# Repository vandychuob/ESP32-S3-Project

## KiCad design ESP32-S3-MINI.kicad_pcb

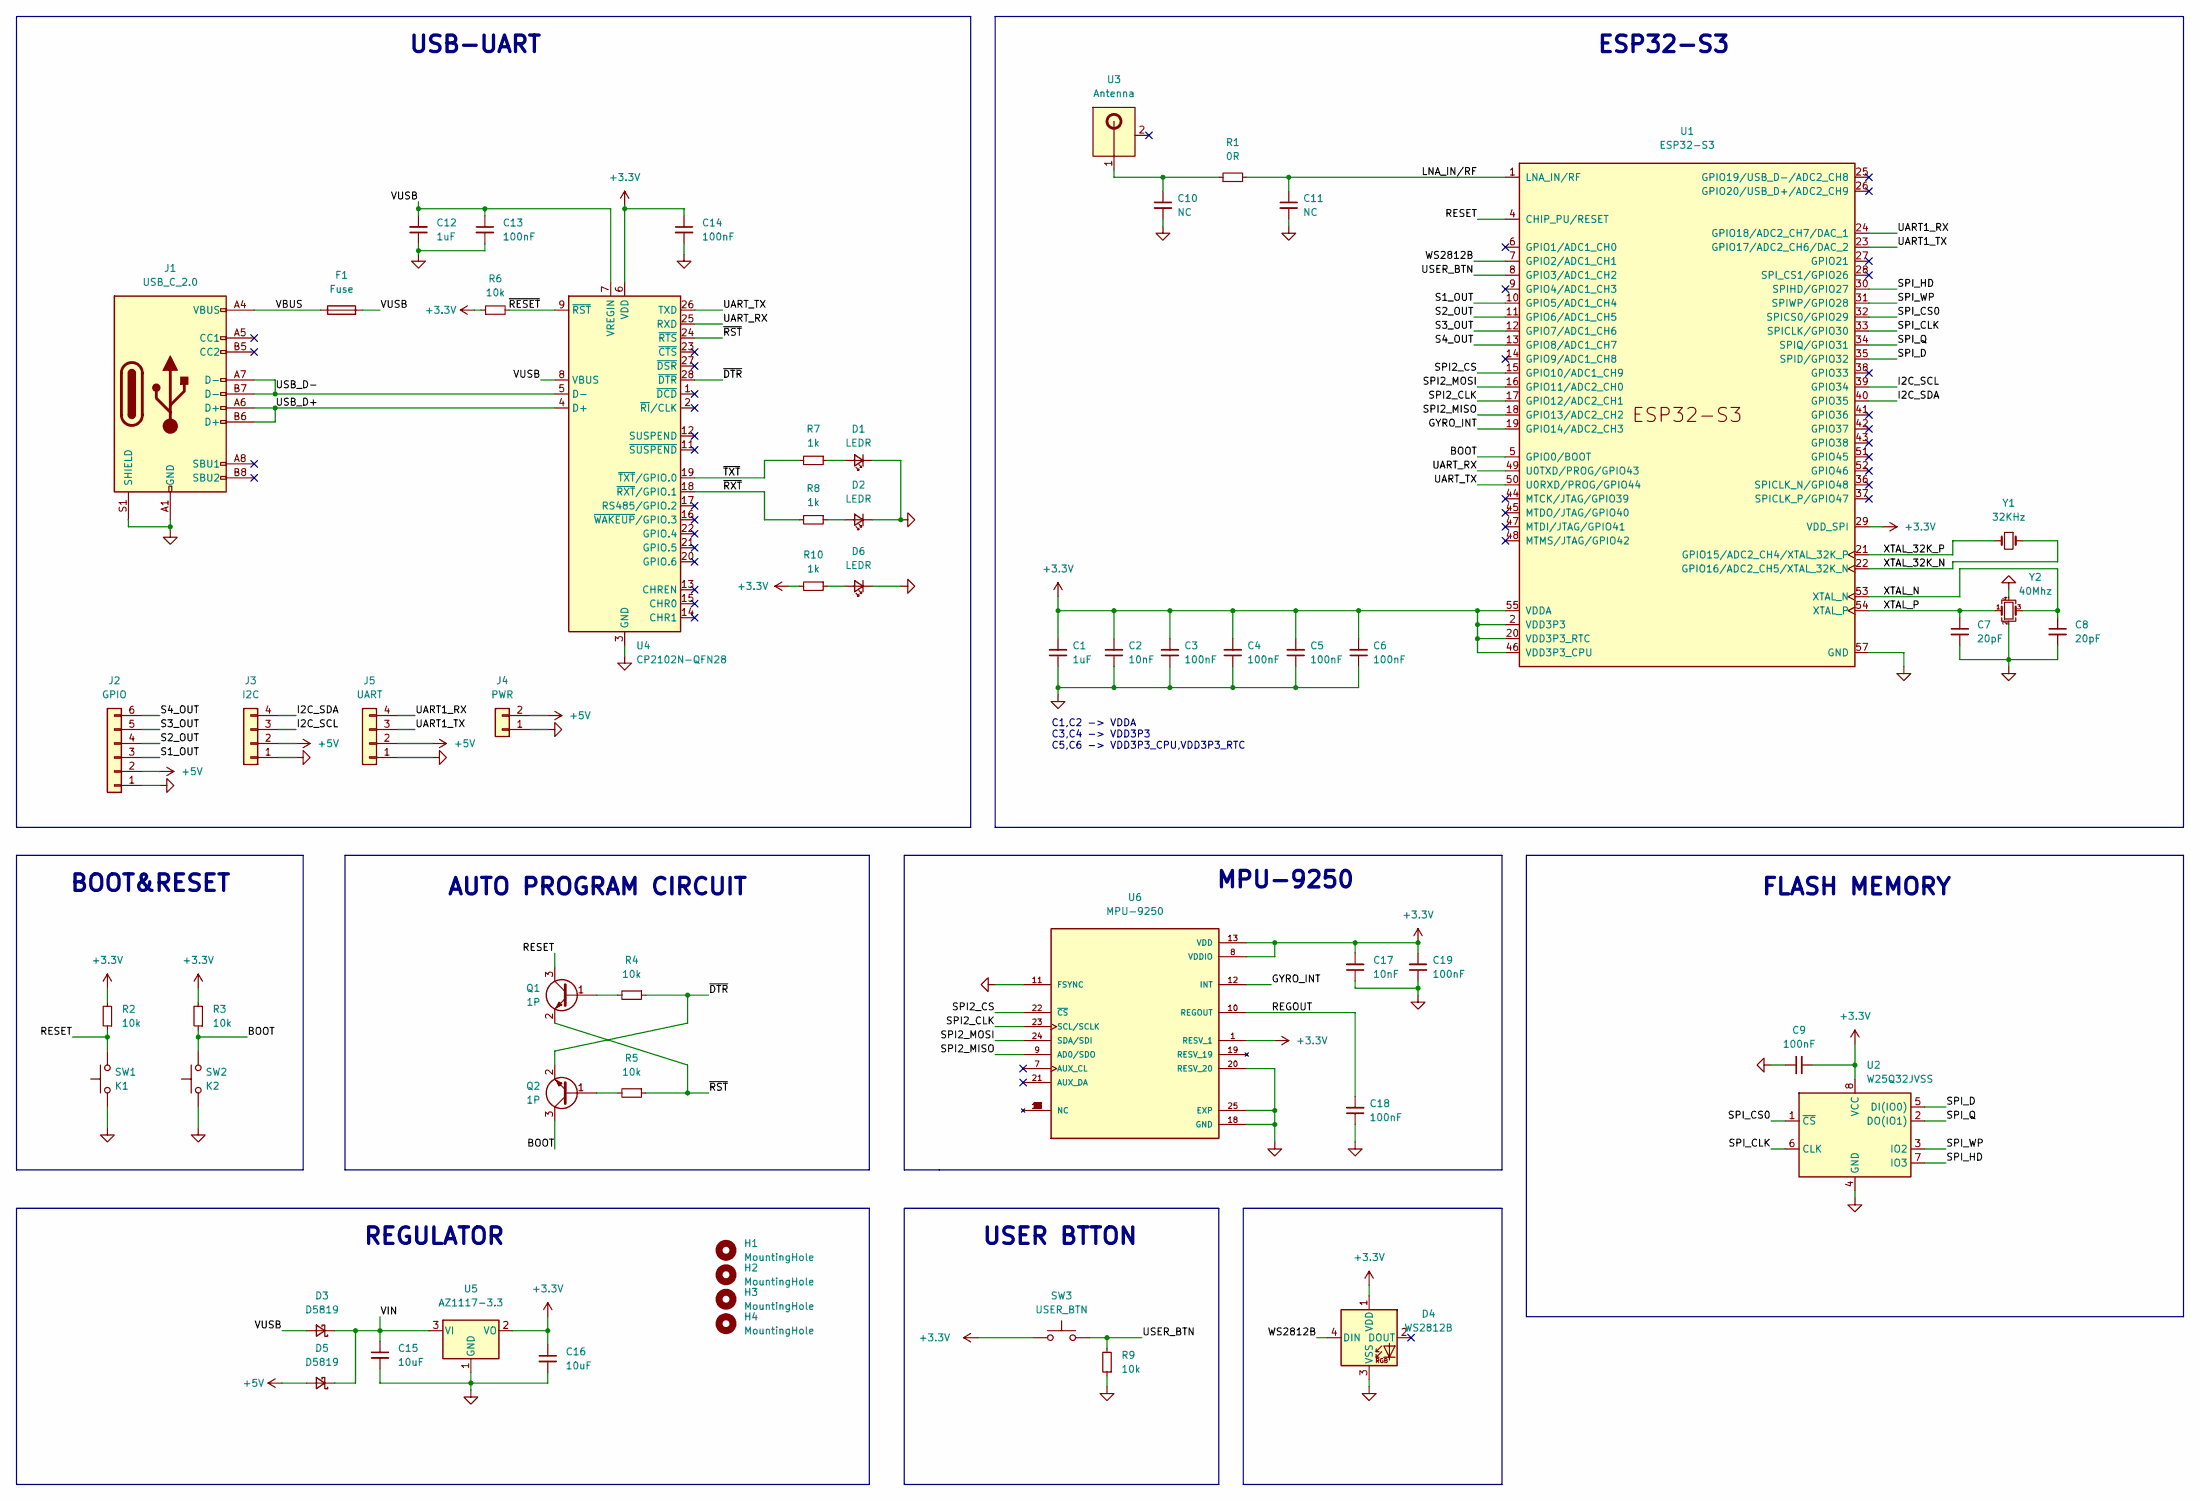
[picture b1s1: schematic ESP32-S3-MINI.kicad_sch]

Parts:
C1, C12: 1uF; C_0603_1608Metric
C2, C17: 10nF; C_0603_1608Metric
C3, C4, C5, C6, C9, C13, C14, C18, C19: 100nF; C_0603_1608Metric
C7, C8: 20pF; C_0603_1608Metric
C10, C11: NC; C_0603_1608Metric
C15, C16: 10uF; C_0805_2012Metric
D1, D2, D6: LEDR; LED_0603_1608Metric
D3, D5: D5819; D_SOD-123
D4: WS2812B; LED_WS2812B_PLCC4_5.0x5.0mm_P3.2mm
F1: Fuse; Fuse_0805_2012Metric
H1, H2, H3, H4: MountingHole; MountingHole_3mm_Pad
J1: USB_C_2.0; USB_C_Receptacle_Palconn_UTC16-G
J2: GPIO; Molex_Pico-Clasp_202396-0607_1x06-1MP_P1.00mm_Horizontal
J3: I2C; Molex_Pico-Clasp_202396-0407_1x04-1MP_P1.00mm_Horizontal
J4: PWR; Molex_Pico-Clasp_202396-0207_1x02-1MP_P1.00mm_Horizontal
J5: UART; Molex_Pico-Clasp_202396-0407_1x04-1MP_P1.00mm_Horizontal
Q1, Q2: 1P; SOT-23
R1: 0R; R_0603_1608Metric
R2, R3, R4, R5, R6, R9: 10k; R_0603_1608Metric
R7, R8, R10: 1k; R_0603_1608Metric
SW1: K1; SW_Push_1P1T_NO_Vertical_Wuerth_434133025816
SW2: K2; SW_Push_1P1T_NO_Vertical_Wuerth_434133025816
SW3: USER_BTN; SW_Push_1P1T_NO_Vertical_Wuerth_434133025816
U1: ESP32-S3; QFN-56-1EP_7x7mm_P0.4mm_EP5.6x5.6mm
U2: W25Q32JVSS; SOIC-8_5.23x5.23mm_P1.27mm
U3: Antenna
U4: CP2102N-QFN28; QFN-28-1EP_5x5mm_P0.5mm_EP3.35x3.35mm
U5: AZ1117-3.3; SOT-89-3
U6: MPU-9250; QFN40P300X300X105-25N; PARTREV 1.1
Y1: 32KHz; Crystal_SMD_3215-2Pin_3.2x1.5mm
Y2: 40Mhz; Crystal_SMD_3225-4Pin_3.2x2.5mm

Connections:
+3V3: C1.2, C2.2, C3.2, C4.2, C5.2, C6.2, C9.2, C14.1, C16.1, C17.2, C19.2, D4.1 (VDD), R2.2, R3.2, R6.1, R10.2, SW3.1, U1.2 (VDD3P3), U1.3 (VDD3P3), U1.20 (VDD3P3_RTC), U1.29 (VDD_SPI), U1.46 (VDD3P3_CPU), U1.55 (VDDA), U1.56 (VDDA), U2.8 (VCC), U4.6 (VDD), U5.2 (VO), U6.1 (RESV_1), U6.8 (VDDIO), U6.13 (VDD)
+5V: D5.2 (A), J2.2, J3.2, J4.2, J5.2
/BOOT: Q2.3 (C), R3.1, SW2.2, U1.5 (GPIO0/BOOT)
/GYRO_INT: U1.19 (GPIO14/ADC2_CH3), U6.12 (INT)
/I2C_SCL: J3.3, U1.39 (GPIO34)
/I2C_SDA: J3.4, U1.40 (GPIO35)
/LNA_IN/RF: C11.1, R1.2, U1.1 (LNA_IN/RF)
/REGOUT: C18.2, U6.10 (REGOUT)
/RESET: Q1.3 (C), R2.1, SW1.2, U1.4 (CHIP_PU/RESET)
/S1_OUT: J2.3, U1.10 (GPIO5/ADC1_CH4)
/S2_OUT: J2.4, U1.11 (GPIO6/ADC1_CH5)
/S3_OUT: J2.5, U1.12 (GPIO7/ADC1_CH6)
/S4_OUT: J2.6, U1.13 (GPIO8/ADC1_CH7)
/SPI2_CLK: U1.17 (GPIO12/ADC2_CH1), U6.23 (SCL/SCLK)
/SPI2_CS: U1.15 (GPIO10/ADC1_CH9), U6.22 (~CS)
/SPI2_MISO: U1.18 (GPIO13/ADC2_CH2), U6.9 (AD0/SDO)
/SPI2_MOSI: U1.16 (GPIO11/ADC2_CH0), U6.24 (SDA/SDI)
/SPI_CLK: U1.33 (SPICLK/GPIO30), U2.6 (CLK)
/SPI_CS0: U1.32 (SPICS0/GPIO29), U2.1 (~CS)
/SPI_D: U1.35 (SPID/GPIO32), U2.5 (DI(IO0))
/SPI_HD: U1.30 (SPIHD/GPIO27), U2.7 (IO3)
/SPI_Q: U1.34 (SPIQ/GPIO31), U2.2 (DO(IO1))
/SPI_WP: U1.31 (SPIWP/GPIO28), U2.3 (IO2)
/UART1_RX: J5.4, U1.24 (GPIO18/ADC2_CH7/DAC_1)
/UART1_TX: J5.3, U1.23 (GPIO17/ADC2_CH6/DAC_2)
/UART_RX: U1.49 (U0TXD/PROG/GPIO43), U4.25 (RXD)
/UART_TX: U1.50 (U0RXD/PROG/GPIO44), U4.26 (TXD)
/USB_D+: J1.A6 (D+), J1.B6 (D+), U4.4 (D+)
/USB_D-: J1.A7 (D-), J1.B7 (D-), U4.5 (D-)
/USER_BTN: R9.2, SW3.2, U1.8 (GPIO3/ADC1_CH2)
/VBUS: F1.1, J1.A4 (VBUS), J1.A9 (VBUS), J1.B4 (VBUS), J1.B9 (VBUS)
/VIN: C15.1, D3.1 (K), D5.1 (K), U5.3 (VI)
/VUSB: C12.2, C13.1, D3.2 (A), F1.2, U4.7 (VREGIN), U4.8 (VBUS)
/WS2812B: D4.4 (DIN), U1.7 (GPIO2/ADC1_CH1)
/XTAL_32K_N: U1.22 (GPIO16/ADC2_CH5/XTAL_32K_N), Y1.1
/XTAL_32K_P: U1.21 (GPIO15/ADC2_CH4/XTAL_32K_P), Y1.2
/XTAL_N: C8.1, U1.53 (XTAL_N), Y2.3
/XTAL_P: C7.1, U1.54 (XTAL_P), Y2.1
/~DTR: Q2.2 (E), R4.1, U4.28 (~DTR)
/~RESET: R6.2, U4.9 (~RST)
/~RST: Q1.2 (E), R5.1, U4.24 (~RTS)
/~RXT: R8.2, U4.18 (~RXT/GPIO.1)
/~TXT: R7.2, U4.19 (~TXT/GPIO.0)
GND: C1.1, C2.1, C3.1, C4.1, C5.1, C6.1, C7.2, C8.2, C9.1, C10.2, C11.2, C12.1, C13.2, C14.2, C15.2, C16.2, C17.1, C18.1, C19.1, D1.1 (K), D2.1 (K), D4.3 (VSS), D6.1 (K), J1.A1 (GND), J1.A12 (GND), J1.B1 (GND), J1.B12 (GND), J1.S1 (SHIELD), J2.1, J3.1, J4.1, J5.1, R9.1, SW1.1, SW2.1, U1.57 (GND), U2.4 (GND), U4.3 (GND), U4.29 (GND), U5.1 (GND), U6.11 (FSYNC), U6.18 (GND), U6.20 (RESV_20), U6.25 (EXP), Y2.2, Y2.4
unnamed: C10.1, R1.1, U3.1
unnamed: D1.2 (A), R7.1
unnamed: D2.2 (A), R8.1
unnamed: D6.2 (A), R10.1
unnamed: Q1.1 (B), R4.2
unnamed: Q2.1 (B), R5.2

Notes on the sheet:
FLASH MEMORY
USB-UART
AUTO PROGRAM CIRCUIT
BOOT&RESET
ESP32-S3
C1,C2 -> VDDA C3,C4 -> VDD3P3 C5,C6 -> VDD3P3_CPU,VDD3P3_RTC
MPU-9250
USER BTTON
REGULATOR

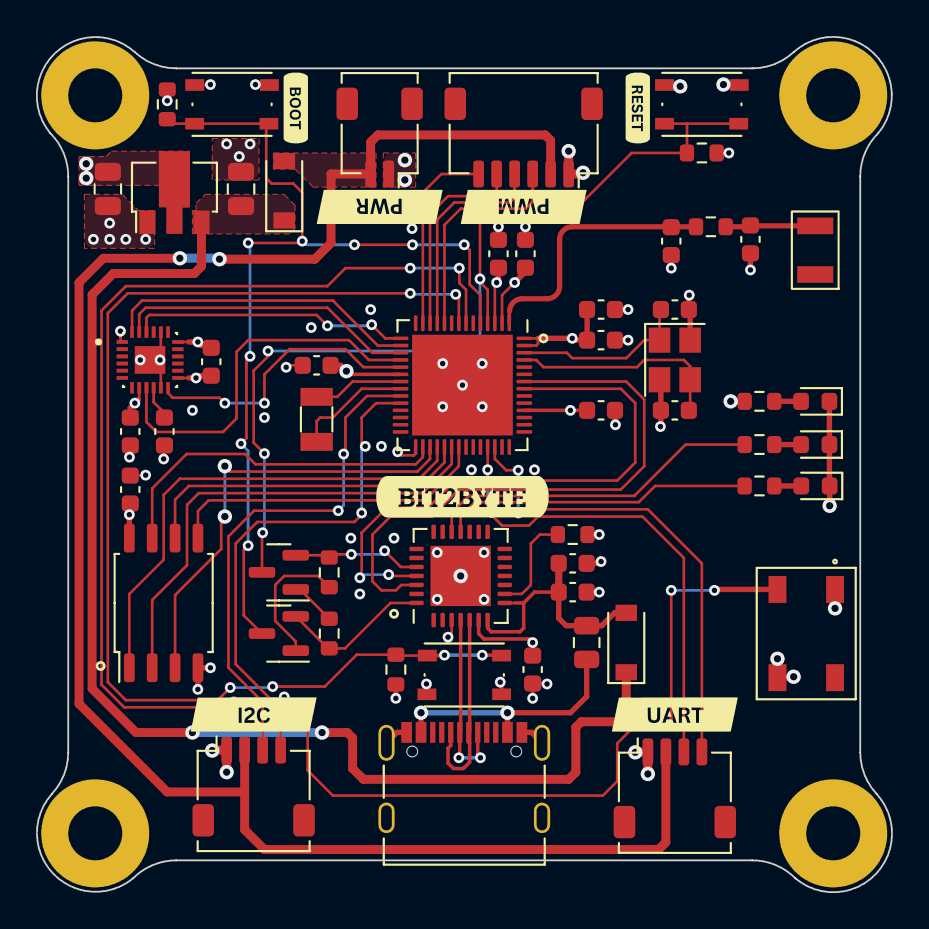
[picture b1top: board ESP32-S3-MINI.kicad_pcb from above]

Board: 4 copper layers, 47.5 x 47.5 mm, 58 parts (0 on the bottom side), 50 nets.

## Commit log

2022-12-14 add project
2022-12-14 remove file
2022-12-14 add datasheet folder
